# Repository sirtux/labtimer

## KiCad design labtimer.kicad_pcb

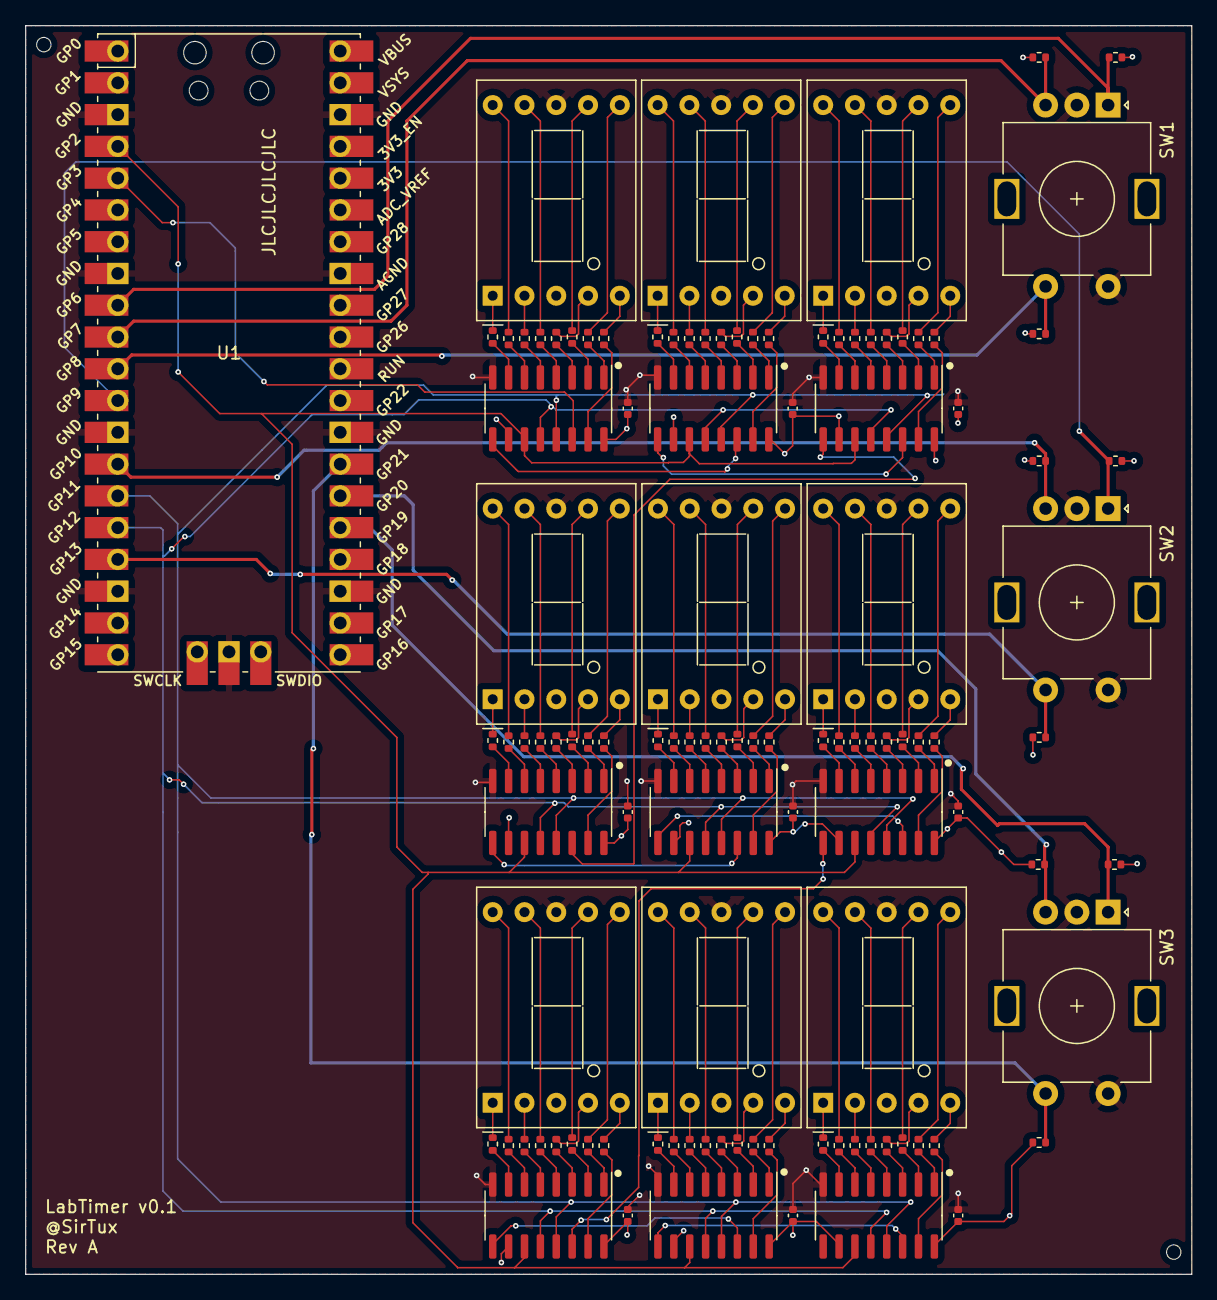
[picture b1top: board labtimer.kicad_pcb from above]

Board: 4 copper layers, 93.2 x 99.8 mm, 114 parts (0 on the bottom side), 167 nets.

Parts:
C1, C2, C3, C4, C5, C6, C7, C8, C9: 100n; C_0402_1005Metric
H1, H2: MountingHole; ToolingHole_JLCSMT
R1, R2, R3, R4, R5, R6, R7, R8, R9, R10, R11, R12, R13, R14, R15, R16, R17, R18, R19, R20, R21, R22, R23, R24, R25, R26, R27, R28, R29, R30, R31, R32, R33, R34, R35, R36, R37, R38, R39, R40, R41, R42, R43, R44, R45, R46, R47, R48, R49, R50, R51, R52, R53, R54, R55, R56, R57, R58, R59, R60, R61, R62, R63, R64, R65, R66, R67, R68, R69, R70, R71, R72: 120; R_0402_1005Metric
R73, R74, R75, R76, R77, R78, R79, R80, R81: 5.1k; R_0402_1005Metric
SW1, SW2, SW3: RotaryEncoder_Switch; RotaryEncoder_Alps_EC11E-Switch_Vertical_H20mm
U1: Pico; RPi_Pico_SMD_TH
U2, U4, U6, U8, U10, U12, U14, U16, U18: 74HC595; SOIC-16_3.9x9.9mm_P1.27mm
U3, U5, U7, U9, U11, U13, U15, U17, U19: D168K; D1X8K

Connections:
+3.3V: C1.1, C2.1, C3.1, C4.1, C5.1, C6.1, C7.1, C8.1, C9.1, R73.1, R74.1, R75.2, R76.1, R77.1, R78.2, R79.1, R80.1, R81.2, U1.36 (3V3), U2.10 (~SRCLR), U2.16 (VCC), U4.10 (~SRCLR), U4.16 (VCC), U6.10 (~SRCLR), U6.16 (VCC), U8.10 (~SRCLR), U8.16 (VCC), U10.10 (~SRCLR), U10.16 (VCC), U12.10 (~SRCLR), U12.16 (VCC), U14.10 (~SRCLR), U14.16 (VCC), U16.10 (~SRCLR), U16.16 (VCC), U18.10 (~SRCLR), U18.16 (VCC)
/Digit1/DATA_OUT: U2.9 (QH'), U4.14 (SER)
/Digit2/DATA_OUT: U4.9 (QH'), U6.14 (SER)
/Digit3/DATA_OUT: U6.9 (QH'), U8.14 (SER)
/Digit4/DATA_OUT: U8.9 (QH'), U10.14 (SER)
/Digit5/DATA_OUT: U10.9 (QH'), U12.14 (SER)
/Digit6/DATA_OUT: U12.9 (QH'), U14.14 (SER)
/Digit7/DATA_OUT: U14.9 (QH'), U16.14 (SER)
/Digit8/DATA_OUT: U16.9 (QH'), U18.14 (SER)
/SPIO_TX: U1.5 (GPIO3), U2.14 (SER)
/SW1_A: R73.2, SW1.A, U1.9 (GPIO6)
/SW1_B: R74.2, SW1.B, U1.10 (GPIO7)
/SW1_S: R75.1, SW1.S1, U1.11 (GPIO8)
/SW2_A: R76.2, SW2.A, U1.12 (GPIO9)
/SW2_B: R77.2, SW2.B, U1.14 (GPIO10)
/SW2_S: R78.1, SW2.S1, U1.17 (GPIO13)
/SW3_A: R79.2, SW3.A, U1.25 (GPIO19)
/SW3_B: R80.2, SW3.B, U1.26 (GPIO20)
/SW3_S: R81.1, SW3.S1, U1.27 (GPIO21)
GND: C1.2, C2.2, C3.2, C4.2, C5.2, C6.2, C7.2, C8.2, C9.2, SW1.C, SW1.S2, SW2.C, SW2.S2, SW3.C, SW3.S2, U1.3 (GND), U1.8 (GND), U1.13 (GND), U1.18 (GND), U1.23 (GND), U1.28 (GND), U1.33 (AGND), U1.38 (GND), U1.42 (GND), U2.8 (GND), U3.3 (CC), U3.8 (CC), U4.8 (GND), U5.3 (CC), U5.8 (CC), U6.8 (GND), U7.3 (CC), U7.8 (CC), U8.8 (GND), U9.3 (CC), U9.8 (CC), U10.8 (GND), U11.3 (CC), U11.8 (CC), U12.8 (GND), U13.3 (CC), U13.8 (CC), U14.8 (GND), U15.3 (CC), U15.8 (CC), U16.8 (GND), U17.3 (CC), U17.8 (CC), U18.8 (GND), U19.3 (CC), U19.8 (CC)
LATCH: U1.16 (GPIO12), U2.12 (RCLK), U4.12 (RCLK), U6.12 (RCLK), U8.12 (RCLK), U10.12 (RCLK), U12.12 (RCLK), U14.12 (RCLK), U16.12 (RCLK), U18.12 (RCLK)
unnamed: R1.1, U2.15 (QA)
unnamed: R1.2, U3.5 (DP)
unnamed: R2.1, U2.1 (QB)
unnamed: R2.2, U3.6 (B)
unnamed: R3.1, U2.2 (QC)
unnamed: R3.2, U3.7 (A)
unnamed: R4.1, U2.3 (QD)
unnamed: R4.2, U3.4 (C)
unnamed: R5.1, U2.4 (QE)
unnamed: R5.2, U3.9 (F)
unnamed: R6.1, U2.5 (QF)
unnamed: R6.2, U3.2 (D)
unnamed: R7.1, U2.6 (QG)
unnamed: R7.2, U3.10 (G)
unnamed: R8.1, U2.7 (QH)
unnamed: R8.2, U3.1 (E)
unnamed: R9.1, U4.15 (QA)
unnamed: R9.2, U5.5 (DP)
unnamed: R10.1, U4.1 (QB)
unnamed: R10.2, U5.6 (B)
unnamed: R11.1, U4.2 (QC)
unnamed: R11.2, U5.7 (A)
unnamed: R12.1, U4.3 (QD)
unnamed: R12.2, U5.4 (C)
unnamed: R13.1, U4.4 (QE)
unnamed: R13.2, U5.9 (F)
unnamed: R14.1, U4.5 (QF)
unnamed: R14.2, U5.2 (D)
unnamed: R15.1, U4.6 (QG)
unnamed: R15.2, U5.10 (G)
unnamed: R16.1, U4.7 (QH)
unnamed: R16.2, U5.1 (E)
unnamed: R17.1, U6.15 (QA)
unnamed: R17.2, U7.5 (DP)
unnamed: R18.1, U6.1 (QB)
unnamed: R18.2, U7.6 (B)
unnamed: R19.1, U6.2 (QC)
unnamed: R19.2, U7.7 (A)
unnamed: R20.1, U6.3 (QD)
unnamed: R20.2, U7.4 (C)
unnamed: R21.1, U6.4 (QE)
unnamed: R21.2, U7.9 (F)
unnamed: R22.1, U6.5 (QF)
unnamed: R22.2, U7.2 (D)
unnamed: R23.1, U6.6 (QG)
unnamed: R23.2, U7.10 (G)
unnamed: R24.1, U6.7 (QH)
unnamed: R24.2, U7.1 (E)
unnamed: R25.1, U8.15 (QA)
unnamed: R25.2, U9.5 (DP)
unnamed: R26.1, U8.1 (QB)
unnamed: R26.2, U9.6 (B)
unnamed: R27.1, U8.2 (QC)
unnamed: R27.2, U9.7 (A)
unnamed: R28.1, U8.3 (QD)
unnamed: R28.2, U9.4 (C)
unnamed: R29.1, U8.4 (QE)
unnamed: R29.2, U9.9 (F)
unnamed: R30.1, U8.5 (QF)
unnamed: R30.2, U9.2 (D)
unnamed: R31.1, U8.6 (QG)
unnamed: R31.2, U9.10 (G)
unnamed: R32.1, U8.7 (QH)
unnamed: R32.2, U9.1 (E)
unnamed: R33.1, U10.15 (QA)
unnamed: R33.2, U11.5 (DP)
unnamed: R34.1, U10.1 (QB)
unnamed: R34.2, U11.6 (B)
unnamed: R35.1, U10.2 (QC)
unnamed: R35.2, U11.7 (A)
unnamed: R36.1, U10.3 (QD)
unnamed: R36.2, U11.4 (C)
unnamed: R37.1, U10.4 (QE)
unnamed: R37.2, U11.9 (F)
unnamed: R38.1, U10.5 (QF)
unnamed: R38.2, U11.2 (D)
unnamed: R39.1, U10.6 (QG)
unnamed: R39.2, U11.10 (G)
unnamed: R40.1, U10.7 (QH)
unnamed: R40.2, U11.1 (E)
unnamed: R41.1, U12.15 (QA)
unnamed: R41.2, U13.5 (DP)
unnamed: R42.1, U12.1 (QB)
unnamed: R42.2, U13.6 (B)
unnamed: R43.1, U12.2 (QC)
unnamed: R43.2, U13.7 (A)
unnamed: R44.1, U12.3 (QD)
unnamed: R44.2, U13.4 (C)
unnamed: R45.1, U12.4 (QE)
unnamed: R45.2, U13.9 (F)
unnamed: R46.1, U12.5 (QF)
unnamed: R46.2, U13.2 (D)
unnamed: R47.1, U12.6 (QG)
unnamed: R47.2, U13.10 (G)
unnamed: R48.1, U12.7 (QH)
unnamed: R48.2, U13.1 (E)
unnamed: R49.1, U14.15 (QA)
unnamed: R49.2, U15.5 (DP)
unnamed: R50.1, U14.1 (QB)
unnamed: R50.2, U15.6 (B)
unnamed: R51.1, U14.2 (QC)
unnamed: R51.2, U15.7 (A)
unnamed: R52.1, U14.3 (QD)
unnamed: R52.2, U15.4 (C)
unnamed: R53.1, U14.4 (QE)
unnamed: R53.2, U15.9 (F)
unnamed: R54.1, U14.5 (QF)
unnamed: R54.2, U15.2 (D)
unnamed: R55.1, U14.6 (QG)
unnamed: R55.2, U15.10 (G)
unnamed: R56.1, U14.7 (QH)
unnamed: R56.2, U15.1 (E)
unnamed: R57.1, U16.15 (QA)
unnamed: R57.2, U17.5 (DP)
unnamed: R58.1, U16.1 (QB)
unnamed: R58.2, U17.6 (B)
unnamed: R59.1, U16.2 (QC)
unnamed: R59.2, U17.7 (A)
unnamed: R60.1, U16.3 (QD)
unnamed: R60.2, U17.4 (C)
unnamed: R61.1, U16.4 (QE)
unnamed: R61.2, U17.9 (F)
unnamed: R62.1, U16.5 (QF)
unnamed: R62.2, U17.2 (D)
unnamed: R63.1, U16.6 (QG)
unnamed: R63.2, U17.10 (G)
unnamed: R64.1, U16.7 (QH)
unnamed: R64.2, U17.1 (E)
unnamed: R65.1, U18.15 (QA)
unnamed: R65.2, U19.5 (DP)
unnamed: R66.1, U18.1 (QB)
unnamed: R66.2, U19.6 (B)
unnamed: R67.1, U18.2 (QC)
unnamed: R67.2, U19.7 (A)
unnamed: R68.1, U18.3 (QD)
unnamed: R68.2, U19.4 (C)
unnamed: R69.1, U18.4 (QE)
unnamed: R69.2, U19.9 (F)
unnamed: R70.1, U18.5 (QF)
unnamed: R70.2, U19.2 (D)
unnamed: R71.1, U18.6 (QG)
unnamed: R71.2, U19.10 (G)
unnamed: R72.1, U18.7 (QH)
unnamed: R72.2, U19.1 (E)
PWM: U1.15 (GPIO11), U2.13 (~OE), U4.13 (~OE), U6.13 (~OE), U8.13 (~OE), U10.13 (~OE), U12.13 (~OE), U14.13 (~OE), U16.13 (~OE), U18.13 (~OE)
SPI0_SCK: U1.4 (GPIO2), U2.11 (SRCLK), U4.11 (SRCLK), U6.11 (SRCLK), U8.11 (SRCLK), U10.11 (SRCLK), U12.11 (SRCLK), U14.11 (SRCLK), U16.11 (SRCLK), U18.11 (SRCLK)

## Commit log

2023-04-29 Initial release
